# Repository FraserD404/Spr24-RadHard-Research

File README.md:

# Spr24 RadHard Research

## Overview:
EEPROM Control Code for Research

This code initializes EEPROMs on a PCB in select banks and then continuously dumps the data to see if there has been a bit flip.
This code is designed to run on a Raspberry Pi 4 with wiringPi library on a 1 MHz I2C bus.

## Known Issues:
- This is not memory safe as there is no code to free the alloc'd data structures. Only ~24 MB of garbage, however. I plan on fixing this soon.
- This code is prone to segmentation faults if any of the pins are disconnected. I don't know the fix for this.
- A full array dump takes approximately 2 minutes if the 512k dump is done in one pass. This is a limitation of the I2C bus. 
- This code could probably be more efficient time & space complexity-wise. I'll probably optimize this at some point.
- There is no tracking individual bit flips. This would be a reasonably simple implementation but time limits me. I do plan on implementing this.

## Files
Control File: radpicode.c
Test Files: filewriting.c , maybe.c

To compile on a Raspberry Pi: **gcc -o rad radpicode.c -l wiringPi**

Memory Usage: ~25 MB allocated total for 16 EEPROMs

CSV Size: ~1.3 KB over 5 minutes

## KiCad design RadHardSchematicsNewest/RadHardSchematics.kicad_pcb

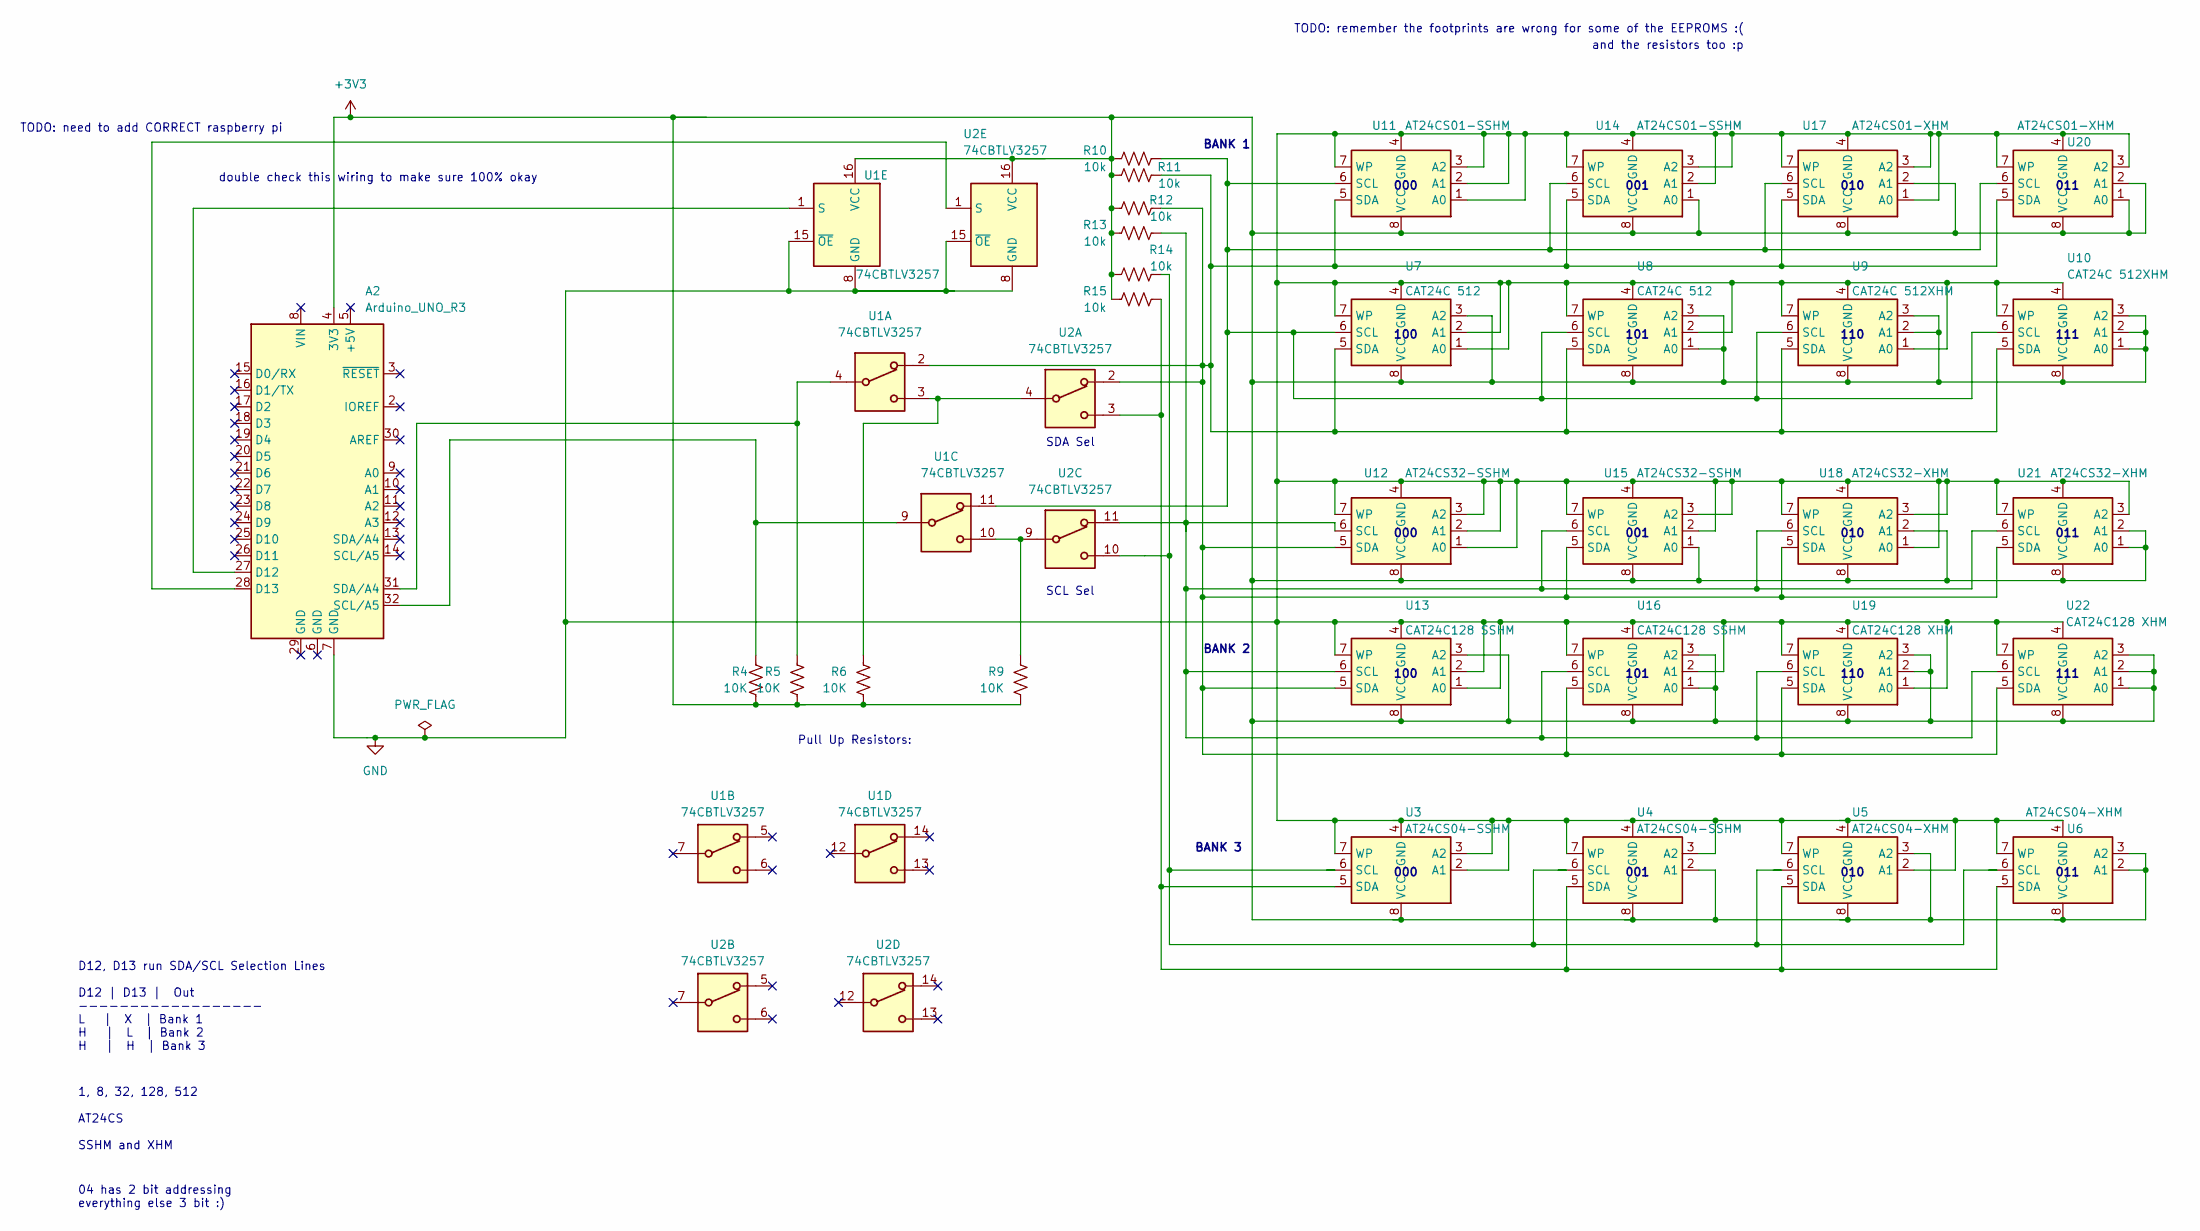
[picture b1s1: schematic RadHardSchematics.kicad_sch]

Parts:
A2: Arduino_UNO_R3
R4, R5, R6, R9: 10K; R_0603_1608Metric
R10, R11, R12, R13, R14, R15: 10k; R_0603_1608Metric
U1, U2: 74CBTLV3257; TSSOP-16_4.4x5mm_P0.65mm
U3, U4: AT24CS04-SSHM; SOIC-8_3.9x4.9mm_P1.27mm
U5, U6: AT24CS04-XHM; TSSOP-8_4.4x3mm_P0.65mm
U7, U8: CAT24C 512; SOIC-8_3.9x4.9mm_P1.27mm
U9, U10: CAT24C 512XHM; TSSOP-8_4.4x3mm_P0.65mm
U11, U14: AT24CS01-SSHM; SOIC-8_3.9x4.9mm_P1.27mm
U12, U15: AT24CS32-SSHM; SOIC-8_3.9x4.9mm_P1.27mm
U13, U16: CAT24C128 SSHM; SOIC-8_3.9x4.9mm_P1.27mm
U17, U20: AT24CS01-XHM; TSSOP-8_4.4x3mm_P0.65mm
U18, U21: AT24CS32-XHM; TSSOP-8_4.4x3mm_P0.65mm
U19, U22: CAT24C128 XHM; TSSOP-8_4.4x3mm_P0.65mm

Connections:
+3V3: A2.4 (3V3), R4.1, R5.1, R6.1, R9.1, R10.1, R11.1, R12.1, R13.1, R14.1, R15.1, U1.16 (VCC), U2.16 (VCC), U3.8 (VCC), U4.2 (A1), U4.8 (VCC), U5.3 (A2), U5.8 (VCC), U6.2 (A1), U6.3 (A2), U6.8 (VCC), U7.3 (A2), U7.8 (VCC), U8.1 (A0), U8.3 (A2), U8.8 (VCC), U9.2 (A1), U9.3 (A2), U9.8 (VCC), U10.1 (A0), U10.2 (A1), U10.3 (A2), U10.8 (VCC), U11.8 (VCC), U12.8 (VCC), U13.3 (A2), U13.8 (VCC), U14.1 (A0), U14.8 (VCC), U15.1 (A0), U15.8 (VCC), U16.1 (A0), U16.3 (A2), U16.8 (VCC), U17.2 (A1), U17.8 (VCC), U18.2 (A1), U18.8 (VCC), U19.2 (A1), U19.3 (A2), U19.8 (VCC), U20.1 (A0), U20.2 (A1), U20.8 (VCC), U21.1 (A0), U21.2 (A1), U21.8 (VCC), U22.1 (A0), U22.2 (A1), U22.3 (A2), U22.8 (VCC)
GND: A2.7 (GND), U1.8 (GND), U1.15 (~OE), U2.8 (GND), U2.15 (~OE), U3.2 (A1), U3.3 (A2), U3.4 (GND), U3.7 (WP), U4.3 (A2), U4.4 (GND), U4.7 (WP), U5.2 (A1), U5.4 (GND), U5.7 (WP), U6.4 (GND), U6.7 (WP), U7.1 (A0), U7.2 (A1), U7.4 (GND), U7.7 (WP), U8.2 (A1), U8.4 (GND), U8.7 (WP), U9.1 (A0), U9.4 (GND), U9.7 (WP), U10.4 (GND), U10.7 (WP), U11.1 (A0), U11.2 (A1), U11.3 (A2), U11.4 (GND), U11.7 (WP), U12.1 (A0), U12.2 (A1), U12.3 (A2), U12.4 (GND), U12.7 (WP), U13.1 (A0), U13.2 (A1), U13.4 (GND), U13.7 (WP), U14.2 (A1), U14.3 (A2), U14.4 (GND), U14.7 (WP), U15.2 (A1), U15.3 (A2), U15.4 (GND), U15.7 (WP), U16.2 (A1), U16.4 (GND), U16.7 (WP), U17.1 (A0), U17.3 (A2), U17.4 (GND), U17.7 (WP), U18.1 (A0), U18.3 (A2), U18.4 (GND), U18.7 (WP), U19.1 (A0), U19.4 (GND), U19.7 (WP), U20.3 (A2), U20.4 (GND), U20.7 (WP), U21.3 (A2), U21.4 (GND), U21.7 (WP), U22.4 (GND), U22.7 (WP)
unnamed: A2.27 (D12), U1.1 (S)
unnamed: A2.28 (D13), U2.1 (S)
unnamed: A2.32 (SCL/A5), R4.2, U1.9
unnamed: A2.31 (SDA/A4), R5.2, U1.4
unnamed: R6.2, U1.3, U2.4
unnamed: R9.2, U1.10, U2.9
unnamed: R14.2, U2.10, U3.6 (SCL), U4.6 (SCL), U5.6 (SCL), U6.6 (SCL)
unnamed: R15.2, U2.3, U3.5 (SDA), U4.5 (SDA), U5.5 (SDA), U6.5 (SDA)
unnamed: R10.2, U1.11, U7.6 (SCL), U8.6 (SCL), U9.6 (SCL), U10.6 (SCL), U11.6 (SCL), U14.6 (SCL), U17.6 (SCL), U20.6 (SCL)
unnamed: R11.2, R12.2, U1.2, U2.2, U7.5 (SDA), U8.5 (SDA), U9.5 (SDA), U10.5 (SDA), U11.5 (SDA), U12.5 (SDA), U13.5 (SDA), U14.5 (SDA), U15.5 (SDA), U16.5 (SDA), U17.5 (SDA), U18.5 (SDA), U19.5 (SDA), U20.5 (SDA), U21.5 (SDA), U22.5 (SDA)
unnamed: R13.2, U2.11, U12.6 (SCL), U13.6 (SCL), U15.6 (SCL), U16.6 (SCL), U18.6 (SCL), U19.6 (SCL), U21.6 (SCL), U22.6 (SCL)

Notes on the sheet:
SCL Sel
BANK 2
011
010
double check this wiring to make sure 100% okay
D12, D13 run SDA/SCL Selection Lines D12 | D13 | Out ------------------ L | X | Bank 1 H | L | Bank 2 H | H | Bank 3
111
001
110
Pull Up Resistors:
101
1, 8, 32, 128, 512 AT24CS SSHM and XHM
TODO: need to add CORRECT raspberry pi
04 has 2 bit addressing everything else 3 bit :)
100
BANK 1
000
TODO: remember the footprints are wrong for some of the EEPROMS :(
SDA Sel
and the resistors too :p
BANK 3

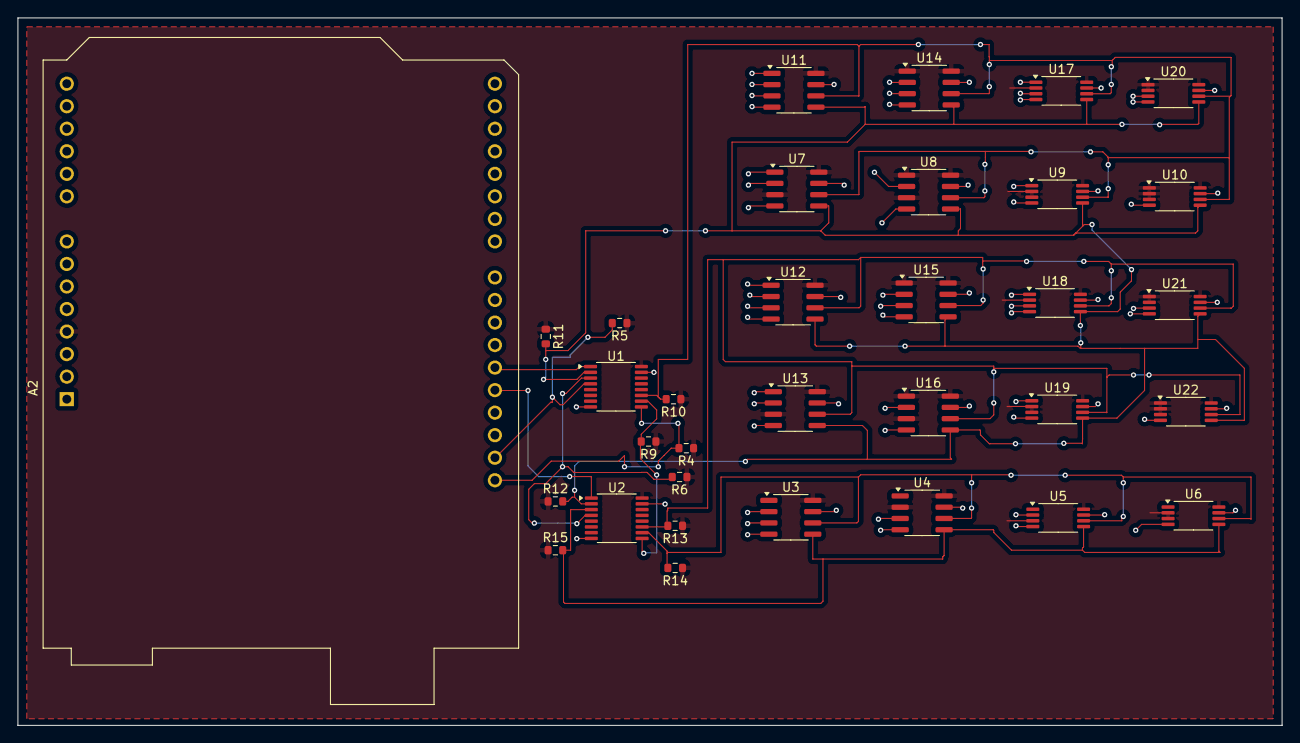
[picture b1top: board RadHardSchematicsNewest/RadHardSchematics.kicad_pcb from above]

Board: 2 copper layers, 142.5 x 79.8 mm, 33 parts (0 on the bottom side), 13 nets.

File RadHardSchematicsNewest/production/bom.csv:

Designator,Footprint,Quantity,Value,LCSC Part #
A2,Arduino_UNO_R3,1,Arduino_UNO_R3,
"R10, R11, R12, R13, R14, R15, R4, R5, R6, R9",0603,10,10k,
"U1, U2",TSSOP-16_4.4x5mm_P0.65mm,2,74CBTLV3257,
"U10, U9",TSSOP-8_4.4x3mm_P0.65mm,2,CAT24C 512XHM,
"U11, U14",SOIC-8_3.9x4.9mm_P1.27mm,2,AT24CS01-SSHM,
"U12, U15",SOIC-8_3.9x4.9mm_P1.27mm,2,AT24CS32-SSHM,
"U13, U16",SOIC-8_3.9x4.9mm_P1.27mm,2,CAT24C128 SSHM,
"U17, U20",TSSOP-8_4.4x3mm_P0.65mm,2,AT24CS01-XHM,
"U18, U21",TSSOP-8_4.4x3mm_P0.65mm,2,AT24CS32-XHM,
"U19, U22",TSSOP-8_4.4x3mm_P0.65mm,2,CAT24C128 XHM,
"U3, U4",SOIC-8_3.9x4.9mm_P1.27mm,2,AT24CS04-SSHM,
"U5, U6",TSSOP-8_4.4x3mm_P0.65mm,2,AT24CS04-XHM,
"U7, U8",SOIC-8_3.9x4.9mm_P1.27mm,2,CAT24C 512,

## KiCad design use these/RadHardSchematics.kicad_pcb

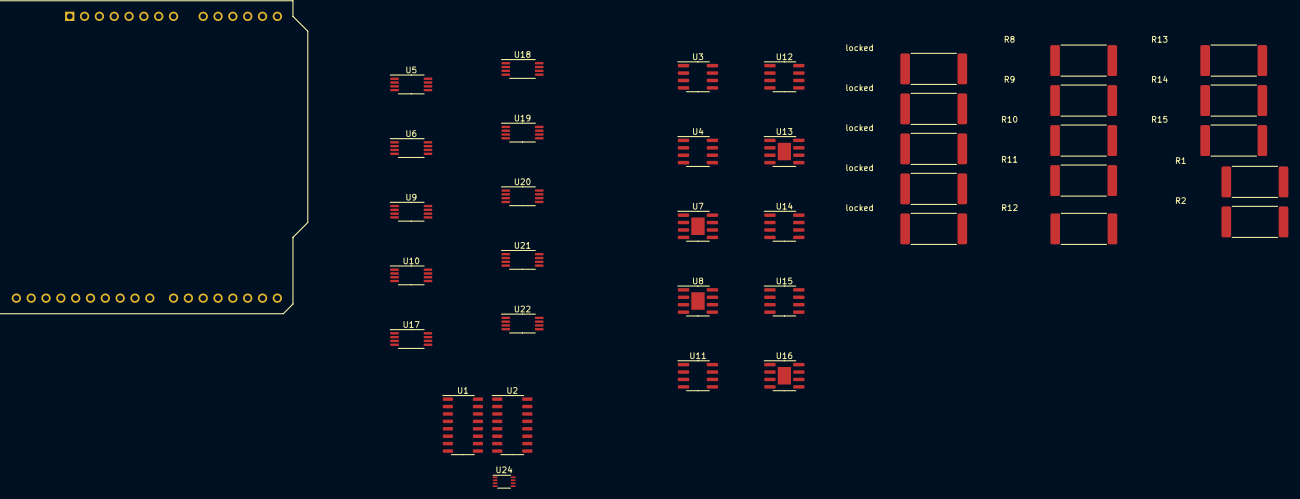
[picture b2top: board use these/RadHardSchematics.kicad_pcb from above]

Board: 2 copper layers, 39 parts (0 on the bottom side), 16 nets, no tracks yet.

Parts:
A1: Arduino_UNO_R3
R1, R2, R8, R9: 10K; R_4020_10251Metric_Pad1.65x5.30mm_HandSolder
R10, R11, R12, R13, R14, R15: 10k; R_4020_10251Metric_Pad1.65x5.30mm_HandSolder
U1, U2: 74CBTLV3257; SO-16_3.9x9.9mm_P1.27mm
U3, U4: AT24CS04-SSHM; SOIC-8_3.9x4.9mm_P1.27mm
U5, U6: AT24CS04-XHM; TSSOP-8_4.4x3mm_P0.65mm
U7, U8: CAT24C 512; SOIC-8-1EP_3.9x4.9mm_P1.27mm_EP2.29x3mm
U9, U10: CAT24C 512XHM; TSSOP-8_4.4x3mm_P0.65mm
U11, U14: AT24CS01-SSHM; SOIC-8_3.9x4.9mm_P1.27mm
U12, U15: AT24CS32-SSHM; SOIC-8_3.9x4.9mm_P1.27mm
U13, U16: CAT24C128 SSHM; SOIC-8-1EP_3.9x4.9mm_P1.27mm_EP2.29x3mm
U17, U20: AT24CS01-XHM; TSSOP-8_4.4x3mm_P0.65mm
U18, U21: AT24CS32-XHM; TSSOP-8_4.4x3mm_P0.65mm
U19, U22: CAT24C128 XHM; TSSOP-8_4.4x3mm_P0.65mm
U24: PCA9306DC; VSSOP-8_2.3x2mm_P0.5mm
locked: 10K; R_4020_10251Metric_Pad1.65x5.30mm_HandSolder
locked#2, locked#4, locked#5: 10K; R_4020_10251Metric_Pad1.65x5.30mm_HandSolder
locked#3: 200k; R_4020_10251Metric_Pad1.65x5.30mm_HandSolder

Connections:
unnamed: A1.4 (3V3), R1.2, R2.1, R8.1, R9.1, R10.1, R11.1, R12.1, R13.1, R14.1, R15.1, U1.16 (VCC), U2.16 (VCC), U3.8 (VCC), U4.2 (A1), U4.8 (VCC), U5.3 (A2), U5.8 (VCC), U6.2 (A1), U6.3 (A2), U6.8 (VCC), U7.3 (A2), U7.8 (VCC), U8.1 (A0), U8.3 (A2), U8.8 (VCC), U9.2 (A1), U9.3 (A2), U9.8 (VCC), U10.1 (A0), U10.2 (A1), U10.3 (A2), U10.8 (VCC), U11.8 (VCC), U12.8 (VCC), U13.3 (A2), U13.8 (VCC), U14.1 (A0), U14.8 (VCC), U15.1 (A0), U15.8 (VCC), U16.1 (A0), U16.3 (A2), U16.8 (VCC), U17.2 (A1), U17.8 (VCC), U18.2 (A1), U18.8 (VCC), U19.2 (A1), U19.3 (A2), U19.8 (VCC), U20.1 (A0), U20.2 (A1), U20.8 (VCC), U21.1 (A0), U21.2 (A1), U21.8 (VCC), U22.1 (A0), U22.2 (A1), U22.3 (A2), U22.8 (VCC), U24.2 (VREF1), locked.1, locked#2.1, locked#3.1, locked#4.1, locked#5.1
unnamed: A1.5 (+5V), U24.7 (VREF2)
unnamed: A1.27 (D12), U1.1 (S)
unnamed: A1.28 (D13), U2.1 (S)
unnamed: U1.3, U2.4, locked.2
unnamed: R14.2, U2.10, U3.6 (SCL), U4.6 (SCL), U5.6 (SCL), U6.6 (SCL)
unnamed: R15.2, U2.3, U3.5 (SDA), U4.5 (SDA), U5.5 (SDA), U6.5 (SDA)
unnamed: A1.7 (GND), U1.8 (GND), U1.15 (~OE), U2.8 (GND), U2.15 (~OE), U3.2 (A1), U3.3 (A2), U3.4 (GND), U3.7 (WP), U4.3 (A2), U4.4 (GND), U4.7 (WP), U5.2 (A1), U5.4 (GND), U5.7 (WP), U6.4 (GND), U6.7 (WP), U7.1 (A0), U7.2 (A1), U7.4 (GND), U7.7 (WP), U8.2 (A1), U8.4 (GND), U8.7 (WP), U9.1 (A0), U9.4 (GND), U9.7 (WP), U10.4 (GND), U10.7 (WP), U11.1 (A0), U11.2 (A1), U11.3 (A2), U11.4 (GND), U11.7 (WP), U12.1 (A0), U12.2 (A1), U12.3 (A2), U12.4 (GND), U12.7 (WP), U13.1 (A0), U13.2 (A1), U13.4 (GND), U13.7 (WP), U14.2 (A1), U14.3 (A2), U14.4 (GND), U14.7 (WP), U15.2 (A1), U15.3 (A2), U15.4 (GND), U15.7 (WP), U16.2 (A1), U16.4 (GND), U16.7 (WP), U17.1 (A0), U17.3 (A2), U17.4 (GND), U17.7 (WP), U18.1 (A0), U18.3 (A2), U18.4 (GND), U18.7 (WP), U19.1 (A0), U19.4 (GND), U19.7 (WP), U20.3 (A2), U20.4 (GND), U20.7 (WP), U21.3 (A2), U21.4 (GND), U21.7 (WP), U22.4 (GND), U22.7 (WP), U24.1 (GND), U24.8 (EN), locked#3.2
unnamed: R8.2, R10.2, U1.10, U1.11, U2.9, U7.6 (SCL), U8.6 (SCL), U9.6 (SCL), U10.6 (SCL), U11.6 (SCL), U14.6 (SCL), U17.6 (SCL), U20.6 (SCL)
unnamed: R11.2, U1.2, U7.5 (SDA), U8.5 (SDA), U9.5 (SDA), U10.5 (SDA), U11.5 (SDA), U14.5 (SDA), U17.5 (SDA), U20.5 (SDA), locked#5.2
unnamed: R13.2, U2.11, U12.6 (SCL), U13.6 (SCL), U15.6 (SCL), U16.6 (SCL), U18.6 (SCL), U19.6 (SCL), U21.6 (SCL), U22.6 (SCL)
unnamed: R12.2, U2.2, U12.5 (SDA), U13.5 (SDA), U15.5 (SDA), U16.5 (SDA), U18.5 (SDA), U19.5 (SDA), U21.5 (SDA), U22.5 (SDA)
unnamed: U1.9, U24.3 (SCL1), locked#4.2
unnamed: A1.32 (SCL/A5), R2.2, U24.6 (SCL2)
unnamed: U1.4, U24.4 (SDA1), locked#2.2
unnamed: A1.31 (SDA/A4), R1.1, U24.5 (SDA2)

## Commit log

2024-04-05 File Writing Testing
    implemented csv writing, debugged
2024-04-05 Updated radpicode to have file writing
    file writing complete
2024-04-06 Filewriting update
    base software should be okay
2024-04-06 Update radpicode
    Moved updated allocation & control functions to radpi
2024-04-06 fixed bugs (i hope)
    please
2024-04-06 fixed memory issues
    for realises this time
2024-04-06 Functionally Final Code
    finally
2024-04-06 update runtime
2024-04-06 Update structure & readme
    yeah
2024-04-08 Added extras for presentation
2024-04-18 added schematics
2024-04-22 New PCB
2024-07-19 adding comments for future analysis
2024-08-21 latest pcb push
2024-08-22 pushing actual schematics lol
2024-08-22 Added New PCB
2024-08-26 working on software
2024-08-26 Changed Footprints for New PCB
